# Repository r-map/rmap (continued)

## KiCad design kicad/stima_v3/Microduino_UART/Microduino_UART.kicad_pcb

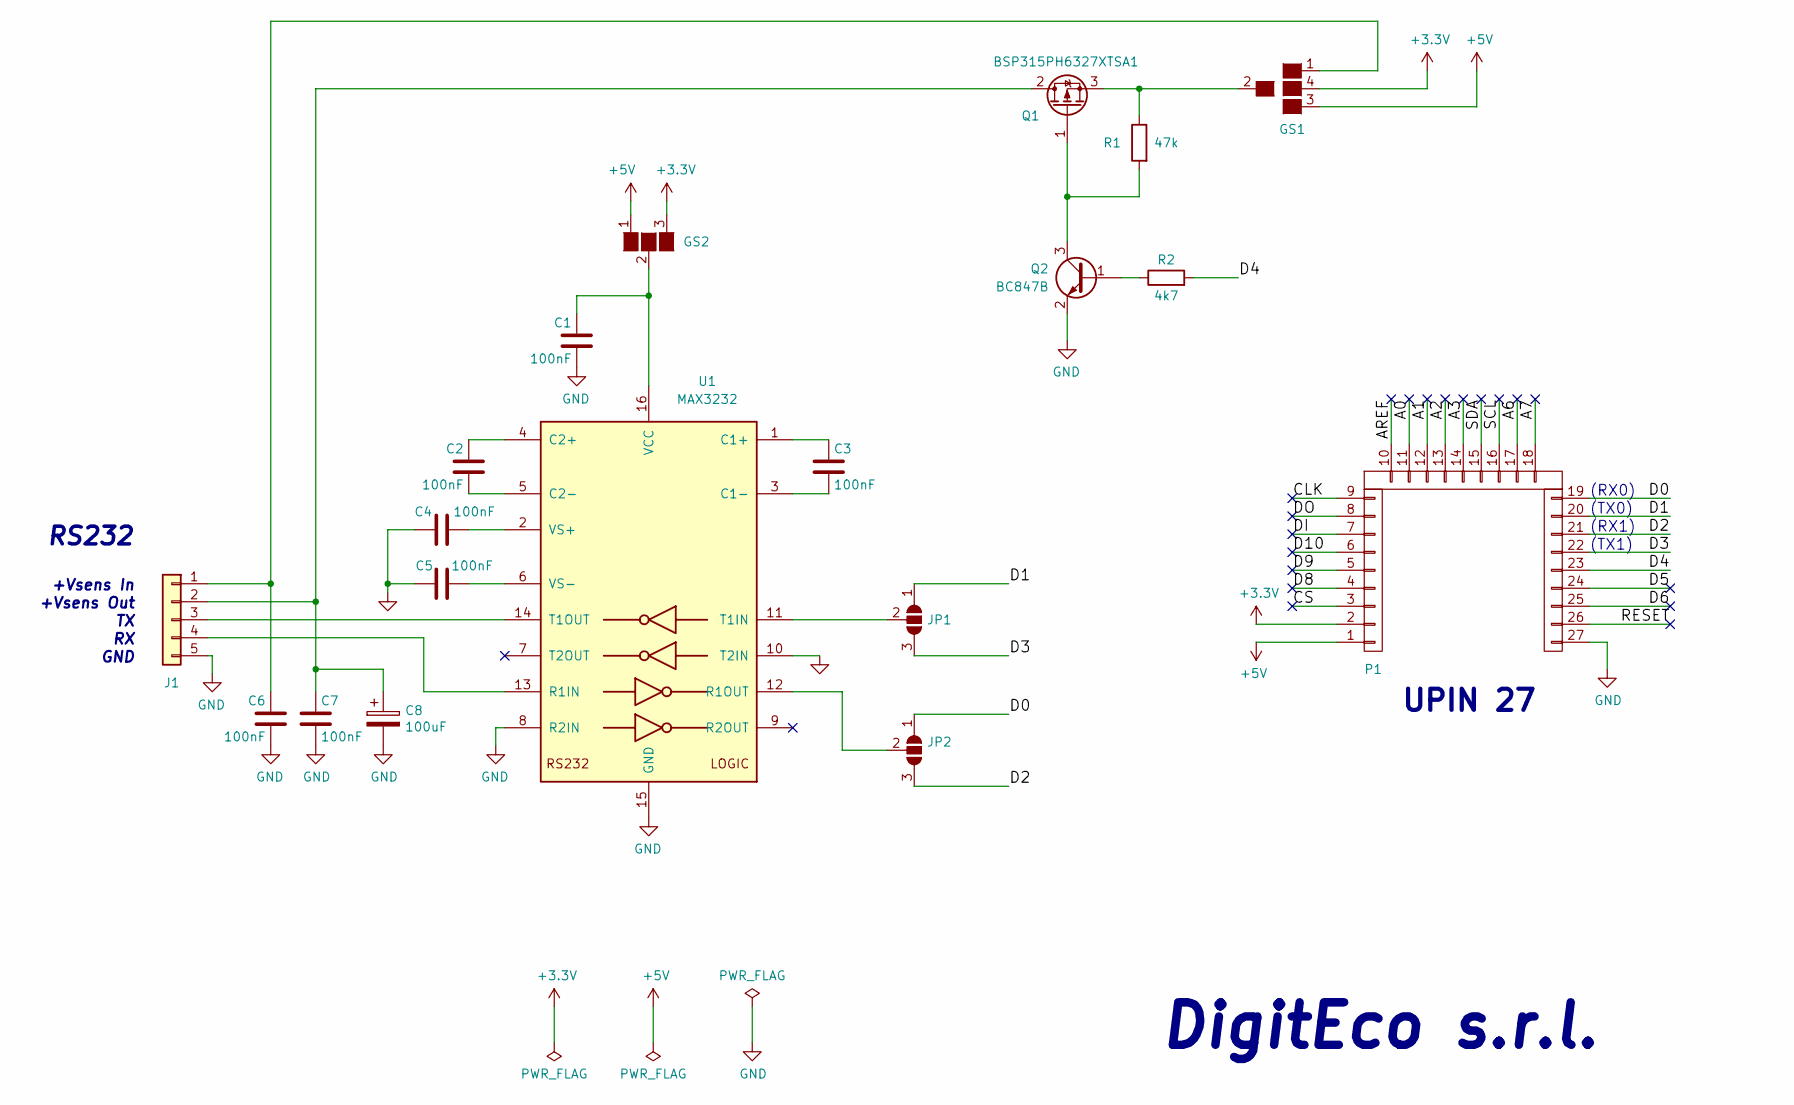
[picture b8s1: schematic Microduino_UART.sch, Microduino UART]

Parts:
C1, C2, C3, C4, C5, C6, C7: 100nF; C_0805_2012Metric
C8: 100uF; CP_Tantalum_Case-B_EIA-3528-21_Reflow
GS1: GS4_b; GS4
GS2: GS3
J1: Conn_01x05; WHURT_5pin_90°_61900511021
JP1, JP2: SolderJumper_3_Open; GS3
P1: CONN_1x27; Upin_27
Q1: BSP315PH6327XTSA1; SOT-223-3_TabPin2
Q2: BC847B; SOT-23
R1: 47k; R_0805_2012Metric
R2: 4k7; R_0805_2012Metric
U1: MAX3232; SOIC-16_3.9x9.9mm_P1.27mm

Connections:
+3V3: GS1.4 (G3), GS2.3 (G3), P1.2
+5V: GS1.3 (G4), GS2.1 (G1), P1.1
/A0: P1.11
/A1: P1.12
/A2: P1.13
/A3: P1.14
/A6: P1.17
/A7: P1.18
/AREF: P1.10
/CLK: P1.9
/CS: P1.3
/D0: JP2.1 (A), P1.19
/D1: JP1.1 (A), P1.20
/D2: JP2.3 (B), P1.21
/D3: JP1.3 (B), P1.22
/D4: P1.23, R2.2
/D5: P1.24
/D6: P1.25
/D8: P1.4
/D9: P1.5
/D10: P1.6
/DI: P1.7
/DO: P1.8
/RESET: P1.26
/SCL: P1.16
/SDA: P1.15
GND: C1.2, C4.1, C5.2, C6.2, C7.2, C8.2, J1.5, P1.27, Q2.2 (E), U1.8 (R2IN), U1.10 (T2IN), U1.15 (GND)
unnamed: C1.1, GS2.2 (G2), U1.16 (VCC)
unnamed: C2.1, U1.4 (C2+)
unnamed: C2.2, U1.5 (C2-)
unnamed: C3.1, U1.1 (C1+)
unnamed: C3.2, U1.3 (C1-)
unnamed: C4.2, U1.2 (VS+)
unnamed: C5.1, U1.6 (VS-)
unnamed: C6.1, GS1.1 (G1), J1.1
unnamed: C7.1, C8.1, J1.2, Q1.2 (D)
unnamed: GS1.2 (G2), Q1.3 (S), R1.1
unnamed: J1.3, U1.14 (T1OUT)
unnamed: J1.4, U1.13 (R1IN)
unnamed: JP1.2 (C), U1.11 (T1IN)
unnamed: JP2.2 (C), U1.12 (R1OUT)
unnamed: Q1.1 (G), Q2.3 (C), R1.2
unnamed: Q2.1 (B), R2.1

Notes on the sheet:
GND
+Vsens Out
RS232
UPIN 27
(RX0)
(TX0)
+Vsens In
(RX1)
(TX1)
DigitEco s.r.l.

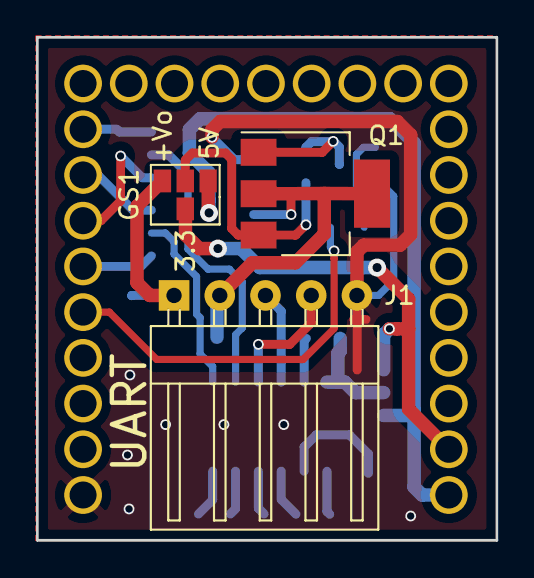
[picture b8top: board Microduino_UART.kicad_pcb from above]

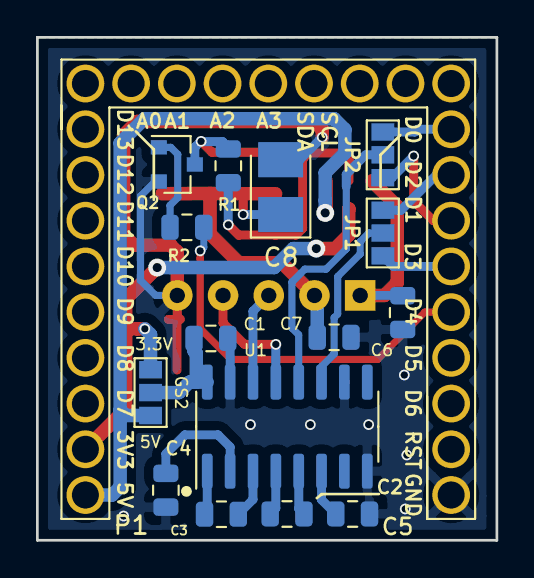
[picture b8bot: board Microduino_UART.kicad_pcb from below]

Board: 2 copper layers, 25.5 x 27.9 mm, 19 parts (16 on the bottom side), 24 nets.

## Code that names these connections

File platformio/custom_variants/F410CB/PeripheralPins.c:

/*
 *******************************************************************************
 * Copyright (c) 2021, STMicroelectronics
 * All rights reserved.
 *
 * This software component is licensed by ST under BSD 3-Clause license,
 * the "License"; You may not use this file except in compliance with the
 * License. You may obtain a copy of the License at:
 *                        opensource.org/licenses/BSD-3-Clause
 *
 *******************************************************************************
 */
/*
 * Automatically generated from STM32F410C(8-B)Tx.xml
 * CubeMX DB release 6.0.10
 */
#include "Arduino.h"
#include "PeripheralPins.h"

/* =====
 * Notes:
 * - The pins mentioned Px_y_ALTz are alternative possibilities which use other
 *   HW peripheral instances. You can use them the same way as any other "normal"
 *   pin (i.e. analogWrite(PA7_ALT1, 128);).
 *
 * - Commented lines are alternative possibilities which are not used per default.
 *   If you change them, you will have to know what you do
 * =====
 */

//*** ADC ***

#ifdef HAL_ADC_MODULE_ENABLED
WEAK const PinMap PinMap_ADC[] = {
  {PA_0, ADC1, STM_PIN_DATA_EXT(STM_MODE_ANALOG, GPIO_NOPULL, 0, 0, 0)}, // ADC1_IN0
  {PA_1, ADC1, STM_PIN_DATA_EXT(STM_MODE_ANALOG, GPIO_NOPULL, 0, 1, 0)}, // ADC1_IN1
  {PA_2, ADC1, STM_PIN_DATA_EXT(STM_MODE_ANALOG, GPIO_NOPULL, 0, 2, 0)}, // ADC1_IN2
  {PA_3, ADC1, STM_PIN_DATA_EXT(STM_MODE_ANALOG, GPIO_NOPULL, 0, 3, 0)}, // ADC1_IN3
  {PA_4, ADC1, STM_PIN_DATA_EXT(STM_MODE_ANALOG, GPIO_NOPULL, 0, 4, 0)}, // ADC1_IN4
  {PA_5, ADC1, STM_PIN_DATA_EXT(STM_MODE_ANALOG, GPIO_NOPULL, 0, 5, 0)}, // ADC1_IN5
  {PA_6, ADC1, STM_PIN_DATA_EXT(STM_MODE_ANALOG, GPIO_NOPULL, 0, 6, 0)}, // ADC1_IN6
  {PA_7, ADC1, STM_PIN_DATA_EXT(STM_MODE_ANALOG, GPIO_NOPULL, 0, 7, 0)}, // ADC1_IN7
  {PB_0, ADC1, STM_PIN_DATA_EXT(STM_MODE_ANALOG, GPIO_NOPULL, 0, 8, 0)}, // ADC1_IN8
  {PB_1, ADC1, STM_PIN_DATA_EXT(STM_MODE_ANALOG, GPIO_NOPULL, 0, 9, 0)}, // ADC1_IN9
  {NC,   NP,   0}
};
#endif

//*** DAC ***

#ifdef HAL_DAC_MODULE_ENABLED
WEAK const PinMap PinMap_DAC[] = {
  {PA_5, DAC1, STM_PIN_DATA_EXT(STM_MODE_ANALOG, GPIO_NOPULL, 0, 1, 0)}, // DAC_OUT1
  {NC,   NP,   0}
};
#endif

//*** I2C ***

#ifdef HAL_I2C_MODULE_ENABLED
WEAK const PinMap PinMap_I2C_SDA[] = {
  {PB_3, I2C2, STM_PIN_DATA(STM_MODE_AF_OD, GPIO_NOPULL, GPIO_AF9_I2C2)},
  {PB_7, I2C1, STM_PIN_DATA(STM_MODE_AF_OD, GPIO_NOPULL, GPIO_AF4_I2C1)},
  {NC,   NP,   0}
};
#endif

#ifdef HAL_I2C_MODULE_ENABLED
WEAK const PinMap PinMap_I2C_SCL[] = {
  {PB_6,  I2C1, STM_PIN_DATA(STM_MODE_AF_OD, GPIO_NOPULL, GPIO_AF4_I2C1)},
  {PB_8,  I2C1, STM_PIN_DATA(STM_MODE_AF_OD, GPIO_NOPULL, GPIO_AF4_I2C1)},
  {PB_10, I2C2, STM_PIN_DATA(STM_MODE_AF_OD, GPIO_NOPULL, GPIO_AF4_I2C2)},
  {NC,    NP,   0}
};
#endif

//*** TIM ***

#ifdef HAL_TIM_MODULE_ENABLED
WEAK const PinMap PinMap_PWM[] = {
  {PA_0,      TIM5, STM_PIN_DATA_EXT(STM_MODE_AF_PP, GPIO_PULLUP, GPIO_AF2_TIM5, 1, 0)}, // TIM5_CH1
  {PA_1,      TIM5, STM_PIN_DATA_EXT(STM_MODE_AF_PP, GPIO_PULLUP, GPIO_AF2_TIM5, 2, 0)}, // TIM5_CH2
  {PA_2,      TIM5, STM_PIN_DATA_EXT(STM_MODE_AF_PP, GPIO_PULLUP, GPIO_AF2_TIM5, 3, 0)}, // TIM5_CH3
  //  {PA_2_ALT1, TIM9, STM_PIN_DATA_EXT(STM_MODE_AF_PP, GPIO_PULLUP, GPIO_AF3_TIM9, 1, 0)}, // TIM9_CH1
  {PA_3,      TIM5, STM_PIN_DATA_EXT(STM_MODE_AF_PP, GPIO_PULLUP, GPIO_AF2_TIM5, 4, 0)}, // TIM5_CH4
  //  {PA_3_ALT1, TIM9, STM_PIN_DATA_EXT(STM_MODE_AF_PP, GPIO_PULLUP, GPIO_AF3_TIM9, 2, 0)}, // TIM9_CH2
  {PA_7,      TIM1, STM_PIN_DATA_EXT(STM_MODE_AF_PP, GPIO_PULLUP, GPIO_AF1_TIM1, 1, 1)}, // TIM1_CH1N
  {PA_8,      TIM1, STM_PIN_DATA_EXT(STM_MODE_AF_PP, GPIO_PULLUP, GPIO_AF1_TIM1, 1, 0)}, // TIM1_CH1
  {PA_9,      TIM1, STM_PIN_DATA_EXT(STM_MODE_AF_PP, GPIO_PULLUP, GPIO_AF1_TIM1, 2, 0)}, // TIM1_CH2
  {PA_10,     TIM1, STM_PIN_DATA_EXT(STM_MODE_AF_PP, GPIO_PULLUP, GPIO_AF1_TIM1, 3, 0)}, // TIM1_CH3
  {PA_11,     TIM1, STM_PIN_DATA_EXT(STM_MODE_AF_PP, GPIO_PULLUP, GPIO_AF1_TIM1, 4, 0)}, // TIM1_CH4
  {PB_0,      TIM1, STM_PIN_DATA_EXT(STM_MODE_AF_PP, GPIO_PULLUP, GPIO_AF1_TIM1, 2, 1)}, // TIM1_CH2N
  {PB_1,      TIM1, STM_PIN_DATA_EXT(STM_MODE_AF_PP, GPIO_PULLUP, GPIO_AF1_TIM1, 3, 1)}, // TIM1_CH3N
  {PB_12,     TIM5, STM_PIN_DATA_EXT(STM_MODE_AF_PP, GPIO_PULLUP, GPIO_AF2_TIM5, 1, 0)}, // TIM5_CH1
  {PB_13,     TIM1, STM_PIN_DATA_EXT(STM_MODE_AF_PP, GPIO_PULLUP, GPIO_AF1_TIM1, 1, 1)}, // TIM1_CH1N
  {PB_14,     TIM1, STM_PIN_DATA_EXT(STM_MODE_AF_PP, GPIO_PULLUP, GPIO_AF1_TIM1, 2, 1)}, // TIM1_CH2N
  {PB_15,     TIM1, STM_PIN_DATA_EXT(STM_MODE_AF_PP, GPIO_PULLUP, GPIO_AF1_TIM1, 3, 1)}, // TIM1_CH3N
  {NC,        NP,   0}
};
#endif

//*** UART ***

#ifdef HAL_UART_MODULE_ENABLED
WEAK const PinMap PinMap_UART_TX[] = {
  {PA_2,  USART2, STM_PIN_DATA(STM_MODE_AF_PP, GPIO_PULLUP, GPIO_AF7_USART2)},
  {PA_9,  USART1, STM_PIN_DATA(STM_MODE_AF_PP, GPIO_PULLUP, GPIO_AF7_USART1)},
  {PA_11, USART6, STM_PIN_DATA(STM_MODE_AF_PP, GPIO_PULLUP, GPIO_AF8_USART6)},
  {PA_15, USART1, STM_PIN_DATA(STM_MODE_AF_PP, GPIO_PULLUP, GPIO_AF7_USART1)},
  {PB_6,  USART1, STM_PIN_DATA(STM_MODE_AF_PP, GPIO_PULLUP, GPIO_AF7_USART1)},
  {NC,    NP,     0}
};
#endif

#ifdef HAL_UART_MODULE_ENABLED
WEAK const PinMap PinMap_UART_RX[] = {
  {PA_3,  USART2, STM_PIN_DATA(STM_MODE_AF_PP, GPIO_PULLUP, GPIO_AF7_USART2)},
  {PA_10, USART1, STM_PIN_DATA(STM_MODE_AF_PP, GPIO_PULLUP, GPIO_AF7_USART1)},
  {PA_12, USART6, STM_PIN_DATA(STM_MODE_AF_PP, GPIO_PULLUP, GPIO_AF8_USART6)},
  {PB_3,  USART1, STM_PIN_DATA(STM_MODE_AF_PP, GPIO_PULLUP, GPIO_AF7_USART1)},
  {PB_7,  USART1, STM_PIN_DATA(STM_MODE_AF_PP, GPIO_PULLUP, GPIO_AF7_USART1)},
  {NC,    NP,     0}
};
#endif

#ifdef HAL_UART_MODULE_ENABLED
WEAK const PinMap PinMap_UART_RTS[] = {
  {PA_1,  USART2, STM_PIN_DATA(STM_MODE_AF_PP, GPIO_PULLUP, GPIO_AF7_USART2)},
  {PA_12, USART1, STM_PIN_DATA(STM_MODE_AF_PP, GPIO_PULLUP, GPIO_AF7_USART1)},
  {NC,    NP,     0}
};
#endif

#ifdef HAL_UART_MODULE_ENABLED
WEAK const PinMap PinMap_UART_CTS[] = {
  {PA_0,  USART2, STM_PIN_DATA(STM_MODE_AF_PP, GPIO_PULLUP, GPIO_AF7_USART2)},
  {PA_11, USART1, STM_PIN_DATA(STM_MODE_AF_PP, GPIO_PULLUP, GPIO_AF7_USART1)},
  {NC,    NP,     0}
};
#endif

//*** SPI ***

#ifdef HAL_SPI_MODULE_ENABLED
WEAK const PinMap PinMap_SPI_MOSI[] = {
  {PA_7,  SPI1, STM_PIN_DATA(STM_MODE_AF_PP, GPIO_PULLUP, GPIO_AF5_SPI1)},
  {PA_10, SPI5, STM_PIN_DATA(STM_MODE_AF_PP, GPIO_PULLUP, GPIO_AF6_SPI5)},
  {PB_5,  SPI1, STM_PIN_DATA(STM_MODE_AF_PP, GPIO_PULLUP, GPIO_AF5_SPI1)},
  {PB_8,  SPI5, STM_PIN_DATA(STM_MODE_AF_PP, GPIO_PULLUP, GPIO_AF6_SPI5)},
  {PB_15, SPI2, STM_PIN_DATA(STM_MODE_AF_PP, GPIO_PULLUP, GPIO_AF5_SPI2)},
  {NC,    NP,   0}
};
#endif

#ifdef HAL_SPI_MODULE_ENABLED
WEAK const PinMap PinMap_SPI_MISO[] = {
  {PA_6,  SPI1, STM_PIN_DATA(STM_MODE_AF_PP, GPIO_PULLUP, GPIO_AF5_SPI1)},
  {PA_12, SPI5, STM_PIN_DATA(STM_MODE_AF_PP, GPIO_PULLUP, GPIO_AF6_SPI5)},
  {PB_4,  SPI1, STM_PIN_DATA(STM_MODE_AF_PP, GPIO_PULLUP, GPIO_AF5_SPI1)},
  {PB_14, SPI2, STM_PIN_DATA(STM_MODE_AF_PP, GPIO_PULLUP, GPIO_AF5_SPI2)},
  {NC,    NP,   0}
};
#endif

#ifdef HAL_SPI_MODULE_ENABLED
WEAK const PinMap PinMap_SPI_SCLK[] = {
  {PA_5,  SPI1, STM_PIN_DATA(STM_MODE_AF_PP, GPIO_PULLUP, GPIO_AF5_SPI1)},
  {PB_0,  SPI5, STM_PIN_DATA(STM_MODE_AF_PP, GPIO_PULLUP, GPIO_AF6_SPI5)},
  {PB_3,  SPI1, STM_PIN_DATA(STM_MODE_AF_PP, GPIO_PULLUP, GPIO_AF5_SPI1)},
  {PB_10, SPI2, STM_PIN_DATA(STM_MODE_AF_PP, GPIO_PULLUP, GPIO_AF5_SPI2)},
  {PB_13, SPI2, STM_PIN_DATA(STM_MODE_AF_PP, GPIO_PULLUP, GPIO_AF5_SPI2)},
  {NC,    NP,   0}
};
#endif

#ifdef HAL_SPI_MODULE_ENABLED
WEAK const PinMap PinMap_SPI_SSEL[] = {
  {PA_4,  SPI1, STM_PIN_DATA(STM_MODE_AF_PP, GPIO_PULLUP, GPIO_AF5_SPI1)},
  {PA_15, SPI1, STM_PIN_DATA(STM_MODE_AF_PP, GPIO_PULLUP, GPIO_AF5_SPI1)},
  {PB_1,  SPI5, STM_PIN_DATA(STM_MODE_AF_PP, GPIO_PULLUP, GPIO_AF6_SPI5)},
  {PB_12, SPI2, STM_PIN_DATA(STM_MODE_AF_PP, GPIO_PULLUP, GPIO_AF5_SPI2)},
  {NC,    NP,   0}
};
#endif

//*** No CAN ***

//*** No ETHERNET ***

//*** No QUADSPI ***

//*** No USB ***

//*** No SD ***

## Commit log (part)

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2024-11-06 i2c-th release 3.20; reset time for SHT to 500 ms
2024-11-06 add crs localrules to disable check on geoimage file dimension for upload
2024-11-09 documentation restructured
2024-11-11 added media files to doc
2024-11-12 added more on citizen science
2024-11-18 feat: first implementation of leaf wetness module
2024-11-25 documentation
2024-11-25 better command line documentation
2024-11-25 updated server configuration
2024-12-27 updated sps30 driver to check fan and laser status with new sps30 firmware
2024-12-28 little better documentation
2025-01-01 pin definition as in wemos D1 mini
2025-01-09 more documentatio on dispense
2025-01-09 more documentatio on server_rmap
2025-01-09 more on DB documentation
2025-01-11 added rmap-manage
2025-01-11 working on model png
2025-01-14 added climatereanalyzer.org
2025-01-14 working on server rmap documentation
2025-01-14 full station modify management
2025-01-16 working on documentation of rmap server implementation
2025-01-27 stimawifi v2 release 20250127
2025-01-27 SensorDriverb migrated to new SPS30 library
2025-01-27 actions now depend on library
2025-01-27 added stimawifi v3 in workflow
2025-02-01 working on server documentation
2025-02-01 server documentatio
2025-02-01 new migration
2025-02-02 server documentation
2025-02-11 dispense
2025-02-17 Update solar_radiation_sensor_task.cpp
    Fix small bug
2025-02-20 fix: wind speed scale from 10 to 100
2025-02-24 feat: updated leaf module with elaborations and init with push button
2025-02-26 feat: elaborate leaf data as count
2025-02-26 fix: count leaf if voltage is lesser than threshold
2025-02-26 minors on dispense doc
2025-03-03 fix: network type reinit on reboot and static params for adc vars
2025-03-05 ported borinud_to 'new' dballe api; WORK IN PROGRESS
2025-03-05 release 17.3: updated translation, no permission for dashboard, new base menu
2025-03-05 updated translation
2025-03-26 revert test_sdcard
2025-03-28 stimawifi: setted heap warning to 3Kb
2025-04-06 math in misure dispensa
2025-04-07 stimawifi howto
2025-04-08 stimawifi release 2025040100
2025-04-15 updated to new ARPAE resouces
2025-04-15 max record number for ARPAE CKAN resouces
2025-04-15 convert from csv files from ARPAE CKAN resouces
2025-04-15 added amqp_producer; rmap release 17.4
2025-04-15 avoid django psycopg2.InterfaceError: connection already closed
2025-04-16 less verbose
2025-04-16 migrated to amqp_producer
2025-04-16 updated DS1307RTC library, added freertos_rtc library and test
2025-04-16 stimawifi i2cmutex for RTC
2025-04-18 DS1307RTC library cleanup
2025-04-18 bugs in ds1307 tests
2025-04-18 stimawifi with RTC
2025-04-19 removed delay in DS1307RTC lib
2025-04-19 delegate freertos device lock to user
2025-04-19 stimawifi RTC mutex protected
2025-04-23 stimawifi release 20250423; log on SDcard and S3 compliant
2025-04-23 filter mobile station type (network) from fixed DB
2025-04-24 rmap release 17.5; borinud and showdata working with mobile data
2025-04-24 improved borinud and showdata working with mobile data
2025-04-24 ident validated as required by WMO bufr
2025-05-05 added status for stimawifi board; changed stimawifi template
2025-05-05 rmap release 17.6
2025-05-05 added publish of station status autodiagnostic
2025-05-05 stimawifi release 20250501
2025-05-05 stima wifi doc updated
2025-05-05 use python 3.9 in github actions
2025-05-05 try to solve riscv32-esp-elf-g++: not found
2025-05-05 try stimawifi with lolin_s3_mini_v3 in Actions
2025-05-05 stimawifi release 20250505
2025-05-06 better granularity for status email; per station activate flag, send to owners that partecipate to a specific group
2025-05-13 RMAP mind map
2025-05-20 slave-leaf and slave-level in V4 workflow
2025-05-21 documentation for stimav4 new modules and sphinx non installed extensions
2025-05-27 gps_lc76g_i2c test
2025-05-27 new stimawifi release
2025-06-09 added How_to_Integrate_ESD into STEM Education in dispense
2025-06-23 test gps_lc76g_i2c ported to STM32
2025-06-25 new stimawifi release: fix platform version, manage two different display
2025-06-25 CI do not work with new platform that require pyhon >= 3.10
2025-06-25 restored rigth CI for stimawifi v3
2025-06-25 stimawifi v3 documentation
2025-06-30 added stimawifi_connect kicad project
2025-06-30 minor formatting error
2025-06-30 wrong httpd conf in monit
2025-07-01 stimawifi release 20250701-0000
2025-07-02 new stimawifi release with better status monitoring
2025-07-02 bug in graphite dballe finder
2025-07-05 Networkclient ported on stack in task; bug in periodic firmware updateù
2025-07-05 Networkclient ported on stack in task; bug in periodic firmware update
2025-07-05 mew stimawifi release
2025-07-07 new stimawifi release: add archive.dat download by web
2025-07-08 new stimawifi release: serve info.dat file too
2025-07-08 stimawifi: group task configuration parameters and shift priority by one
2025-07-08 stimawifi change in task priority
2025-07-08 stimawifi doc: new urls for archive download by jttp
2025-07-17 stimawifi release 202507170000: reduced memory fragmentation for no Guru Meditation Error
2025-07-21 added amqp2ftp prototype
2025-07-22 amqp2ftp completed
2025-07-22 amqp2ftp rename file in ftp to be atomic
2025-07-23 moved custom variants for new playformio compatibility
2025-07-27 fix platform-espressif32 commit for stimawifi
2025-07-28 updated platformio.ini for microduino stm32 variant
2025-08-07 add new line in RPC response for streaming
2025-08-07 added MQTT json rpc to stimawifi
2025-08-07 stimawifi release 2025-08-07T00:00
2025-08-08 define and configure pins for pinout RPC
2025-08-14 rpc recovery work for achive too
2025-08-14 check end of file reading archive in recovery RPC in stimawifi
2025-08-16 stimawifi: working on RPC
2025-08-19 stimawifi release 20250819: RPC management with recovery rpc that do not rearchive messages
2025-08-19 pip install intelhex in stima_v3 workflow
2025-08-19 stimawifi RPC documentation
2025-08-20 updated and added url for zeroconf stimawifi
2025-08-27 dust is not particulate; change description
2025-09-03 new stimawifi release; do not reboot when not recoverable operations are running
2025-09-16 stimawifi new release: less led light, and better reset reason management
2025-09-17 stimawifi release 2025-09-17T00:00 ; bug in publish summary error
2025-09-24 mqtt2stationmaintd manage laststatus
2025-09-24 stimawifi comment for mqtt disconnect management
2025-09-24 manage admin messages over MQTT implementing email alerts
2025-09-24 working on composereportd
2025-09-25 added lock when write on DB
2025-09-26 stimawifi connection board fritzing part
2025-10-01 stimawifi with fritzing
2025-10-01 better sps30 figure
2025-10-02 progetti in doc
2025-10-03 stimawifi fritzing parts
2025-10-04 stimawifi better fritzing schema
2025-10-16 export data from borinud in csv forma; dropdown menu for export format; new python version compatibility
2025-10-16 graphite_dballe python version compatibility
2025-10-20 bugs in mqtt2stationmaintd
2025-10-21 stimawifi release 20251021: retry added to wifi connect and mqtt publish; better management of reconnect; long timeout in wifi connect
2025-10-23 better status email template
2025-10-23 updated locale
2025-10-23 updated italian translation
2025-10-25 stimawifi log RSSI values
2025-10-27 solve xhr mixed block in localdata page mixing https and http
2025-10-27 redirect stationlocaldata url to http
2025-10-27 added summary status for WiFi rssi
2025-10-27 added status for WiFi rssi in template
2025-10-28 better management of memory status
2025-10-28 bug in mqtt status report
2025-10-30 stimawifi release 20251030
2025-11-01 stimawifi: sqlite db increase file size with time; at boot if DB is big and no messages unsent data will be migrated to archive and DB regenerated
2025-11-03 updated Time library to 1.6.1 and changed include to TimeLib.h for windows compatibility
2025-11-15 integrate dispense
2025-11-15 dispensa riscaldamento_globale.rst
2025-11-21 better image in doc
2025-11-22 more doc for dispense
2025-11-23 improve dispensa qualità aria
2025-11-23 added sphinx wagtail theme
2025-11-25 added giustizia climatica in dispense
2025-11-25 new stimawifi release 20251125; added calibration RPC and removed autocalibration for SCD
2026-01-24 not usefull typedef
2026-01-29 added last events in doc
2026-02-04 added Climate-Plunder-EN-Final-Paper in dispense
2026-02-18 removed static variables in ozgps library
2026-02-18 removed global variables in gps*; better error status for gps; topics for admin and rpc in mobile stations
2026-02-18 updated readme gps
2026-02-18 HEAP_MIN_WARNING less of 500byte for mobile stations
2026-02-21 refinements and stable platform version
2026-02-23 stimawifi new release; reduced power for wifi to solve https://github.com/arendst/Tasmota/discussions/15443
2026-02-23 stima V2 CI failed by last commit
2026-02-25 documented event: casa dei risvegli
2026-02-25 wrong image
2026-02-25 bug in laststatus
2026-02-26 RPC for mobile stations
2026-02-26 websocket monitor and RPC for mobile stations
2026-02-26 bug in RPC
2026-02-26 rmap release 17.8
2026-03-04 rmap release 17.9
2026-03-04 allows specifying task affinity in an SMP system in esp32freertos-cpp
2026-03-04 use malloc everywhere in sqlite3
2026-03-04 indicate the index number of the CPU which the task should be pinned to
2026-03-04 refinements
2026-03-04 porting to esp32-S3
2026-03-04 bug in pixel management
2026-03-06 porting to esp32-S3 with thread pinned to core-1 and sqlite-memory allocated by ps_malloc
2026-03-07 tuning configuration for S3; new stimawifi release
2026-03-08 new configuration for exp32-S3; new stimawifi release
2026-03-10 db recovery RPC rewritten as finite statte machine
2026-03-10 manage sdcard error on rpc recovery from DB
2026-03-10 better rpc management
2026-03-12 new stimawifi release; bugs and improvements on recovery rpc
2026-03-15 ESP32-S3 replace ESP32-C3
2026-03-15 bug in migration
2026-03-16 new stimawifi release: new strategy for vacuum
2026-03-17 LC76G GPS module used by I2C bus
2026-03-18 new stimawifi release: bug in GPS Serial
2026-03-20 documentated gpsdRelay and CO2 calibration RPC
2026-03-27 stimawifi: added gps_i2c_thread for GPS via I2C bus
2026-03-27 bug in test gps via I2C
2026-03-27 stimawifi with platform-espressif32 tasmota releases 2026.03.30
2026-03-31 stimawifi better GPS management
2026-03-31 minor
2026-04-11 bug in insertnewstation: failed check for fixed stations
2026-04-11 new rmap release
2026-04-16 added test_sdcard_esp32
2026-04-21 stimawifi use two queue for publish with different priority
2026-04-22 stimawifi: distribute all bins
2026-04-23 better stimawifi documentation
2026-04-23 stimawifi build firmware
2026-04-24 stimawifi: change in queue configuration
2026-04-26 stimawifi: new release with recovery optimization
2026-04-26 added laboratori to documentation tree
2026-04-27 working on stimawifi hoto
2026-04-27 working on stimawifi howto
2026-04-29 more on biometeorologia dispensa
2026-04-30 added recovery transaction management using a special message traveling around the queues
2026-05-04 stimawifi base board doc
2026-05-14 wrong units in btable for particulate matter
2026-05-14 Revert "wrong units in btable for particulate matter"
    This reverts commit 968d4004c02580ab6e071cab875656cf97667459.
2026-05-14 Reapply "wrong units in btable for particulate matter"
    This reverts commit b8b2c0f2b0fd7a1dadae1715ca7699c01fe33dc7.
2026-05-14 fix: V-001 security vulnerability
    Automated security fix generated by Orbis Security AI
2026-05-15 SPS30: added clean cycle at startup and every day; new stimawiwi release
2026-06-11 wrong RPC calibrate in doc
2026-06-11 new cable color for stimawifi v3
2026-06-12 wrong cable color for sht85
2026-06-16 stimawifi new release: manage publish status for mobile stations
2026-06-16 doc for stimawifi hoto
2026-06-19 use GGA GLL and RMC NMEA record in Serial GPS
2026-06-19 rmap project not ready for stmduino v3
